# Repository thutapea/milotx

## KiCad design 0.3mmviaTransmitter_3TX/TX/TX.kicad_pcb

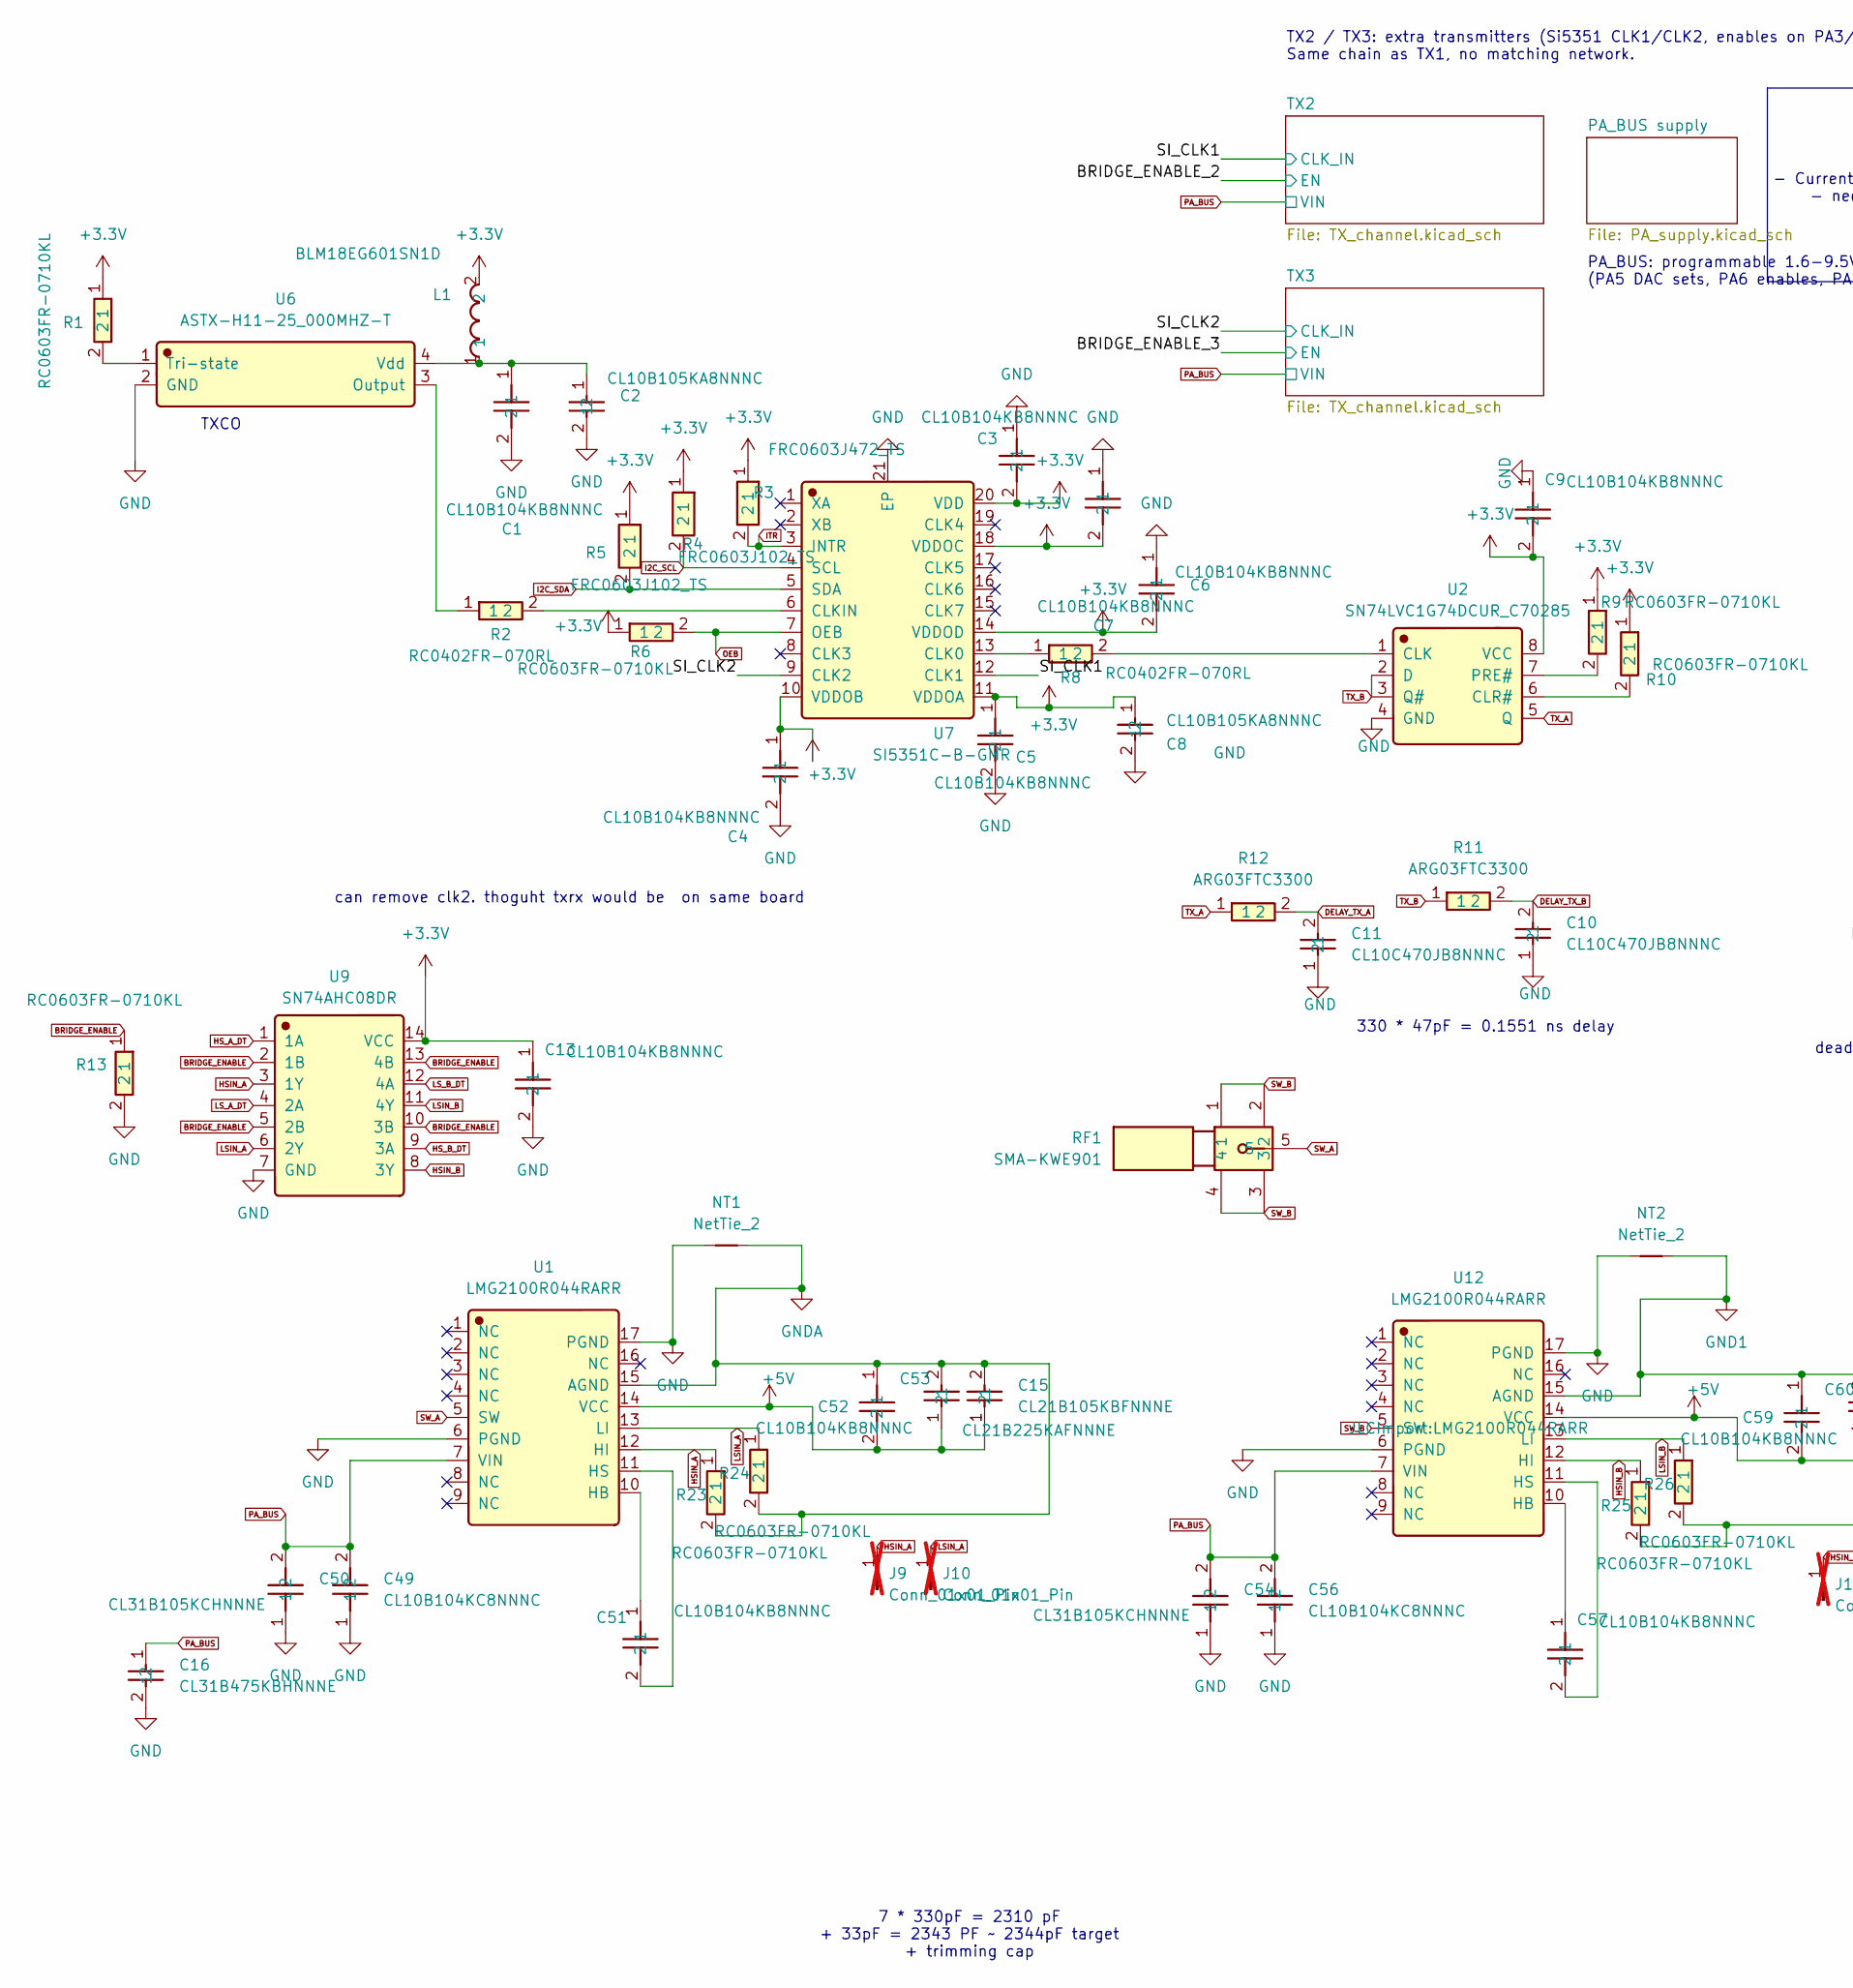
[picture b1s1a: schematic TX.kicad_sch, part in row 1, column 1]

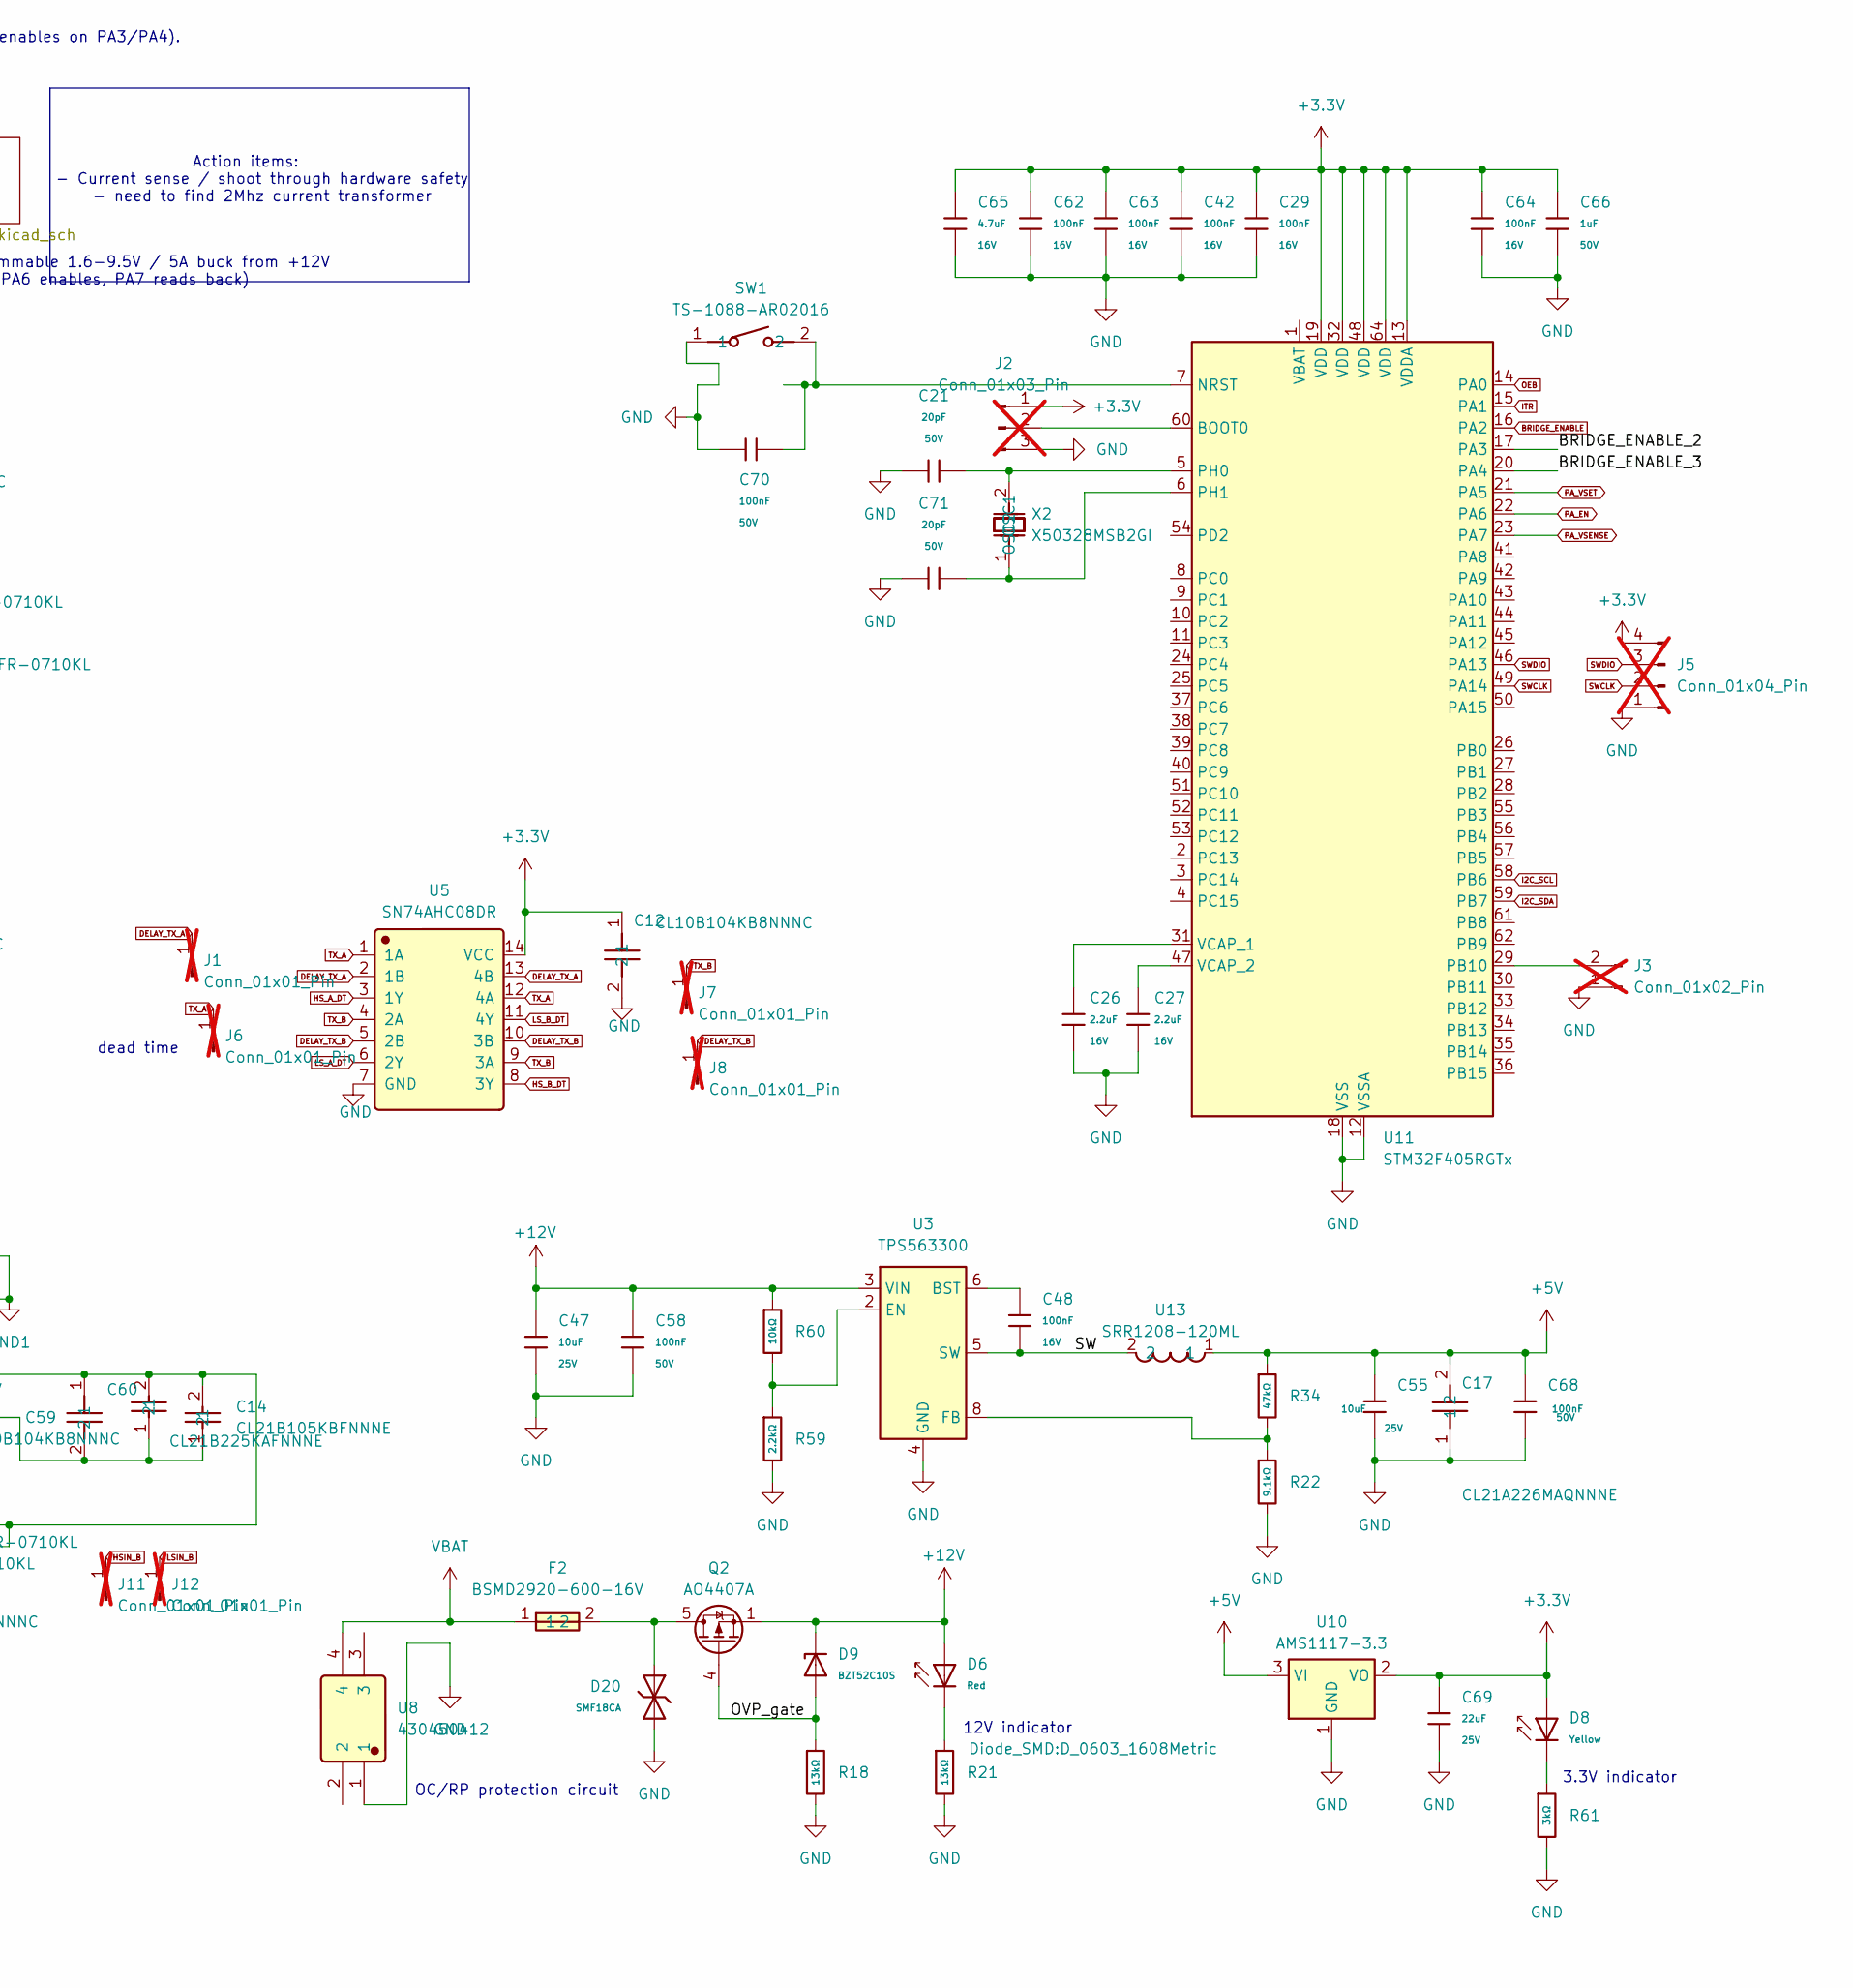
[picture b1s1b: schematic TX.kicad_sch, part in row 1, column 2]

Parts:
C1, C3, C4, C5, C6, C7, C9, C12, C13, C51, C52, C57, C59: CL10B104KB8NNNC; C_0603_1608Metric; Manufacturer Part CL10B104KB8NNNC; LCSC C1591
C2, C8: CL10B105KA8NNNC; C_0603_1608Metric; Manufacturer Part CL10B105KA8NNNC; LCSC C29936
C10, C11: CL10C470JB8NNNC; C_0603_1608Metric; Manufacturer Part CL10C470JB8NNNC; LCSC C1671
C14, C15: CL21B105KBFNNNE; C_0805_2012Metric; Manufacturer Part CL21B105KBFNNNE; LCSC C28323
C16: CL31B475KBHNNNE; C_1206_3216Metric; Manufacturer Part CL31B475KBHNNNE; LCSC C51205
C17: CL21A226MAQNNNE; C_0805_2012Metric; Manufacturer Part CL21A226MAQNNNE; LCSC C45783
C21, C71: 20pF; C_0402_1005Metric; Voltage Rated 50V; Tolerance ±5%; Part 0402CG200J500NT; LCSC C1554
C26, C27: 2.2uF; C_0603_1608Metric; Voltage Rated 16V; Tolerance ±10%; Part CL10A225KO8NNNC; LCSC C23630
C29, C42, C48, C62, C63, C64: 100nF; C_0402_1005Metric; Voltage Rated 16V; Tolerance ±10%; Part CL05B104KO5NNNC; LCSC C1525
C47, C55: 10uF; C_0603_1608Metric; Voltage Rated 25V; Tolerance ±20%; Part CL10A106MA8NRNC; LCSC C96446
C49, C56: CL10B104KC8NNNC; C_0603_1608Metric; Manufacturer Part CL10B104KC8NNNC; LCSC C15725
C50, C54: CL31B105KCHNNNE; C_1206_3216Metric; Manufacturer Part CL31B105KCHNNNE; LCSC C13832
C53, C60: CL21B225KAFNNNE; C_0805_2012Metric; Manufacturer Part CL21B225KAFNNNE; LCSC C19110
C58, C68, C70: 100nF; C_0603_1608Metric; Voltage Rated 50V; Tolerance ±10%; Part CC0603KRX7R9BB104; LCSC C14663
C65: 4.7uF; C_0603_1608Metric; Voltage Rated 16V; Tolerance ±10%; Part CL10A475KO8NNNC; LCSC C19666
C66: 1uF; C_0603_1608Metric; Voltage Rated 50V; Tolerance ±10%; Part CL10A105KB8NNNC; LCSC C15849
C69: 22uF; C_0805_2012Metric; Voltage Rated 25V; Tolerance ±20%; Part CL21A226MAQNNNE; LCSC C45783
D6: Red; D_0603_1608Metric; Part KT-0603R; LCSC C2286
D8: Yellow; D_0603_1608Metric; Forward Voltage (VF) 1.6V~2.6V; Part NCD0603Y2; LCSC C89811
D9: BZT52C10S; D_SOD-323; Part BZT52C10S; LCSC C19077446
D20: SMF18CA; D_SOD-123F; Breakdown Voltage 20V; Part SMF18CA; LCSC C19077513
F2: BSMD2920-600-16V; Manufacturer Part BSMD2920-600-16V; LCSC C910847
J1, J6, J7, J8, J9, J10, J11, J12: Conn_01x01_Pin; PinHeader_1x01_P2.54mm_Vertical; not fitted
J2: Conn_01x03_Pin; PinSocket_1x03_P2.54mm_Vertical; not fitted
J3: Conn_01x02_Pin; PinHeader_1x02_P2.54mm_Vertical; not fitted
J5: Conn_01x04_Pin; PinHeader_1x04_P2.54mm_Vertical; not fitted
L1: BLM18EG601SN1D; L_0603_1608Metric; Manufacturer Part BLM18EG601SN1D; LCSC C20345
NT1, NT2: NetTie_2; NetTie-2_SMD_Pad2.0mm
Q2: AO4407A; SOIC-8_3.9x4.9mm_P1.27mm; Manufacturer Part AO4407A; LCSC C2841482
R1, R6, R9, R10, R13, R23, R24, R25, R26: RC0603FR-0710KL; R_0603_1608Metric; Manufacturer Part RC0603FR-0710KL; LCSC C98220
R2, R8: RC0402FR-070RL; R_0402_1005Metric; Manufacturer Part RC0402FR-070RL; LCSC C106231
R3: FRC0603J472_TS; R_0603_1608Metric; Manufacturer Part FRC0603J472 TS; LCSC C2907166
R4, R5: FRC0603J102_TS; R_0603_1608Metric; Manufacturer Part FRC0603J102 TS; LCSC C2907113
R11, R12: ARG03FTC3300; R_0603_1608Metric; Manufacturer Part ARG03FTC3300; LCSC C217969
R18, R21: 13kΩ; R_0603_1608Metric; Overload Voltage (Max) 75V; Tolerance ±1%; Part 0603WAF1302T5E; LCSC C22797
R22: 9.1kΩ; R_0603_1608Metric; Overload Voltage (Max) 75V; Tolerance ±1%; Part 0603WAF9101T5E; LCSC C23260
R34: 47kΩ; R_0402_1005Metric; Overload Voltage (Max) 50V; Tolerance ±1%; Part 0402WGF4702TCE; LCSC C25792
R59: 2.2kΩ; R_0402_1005Metric; Overload Voltage (Max) 50V; Tolerance ±1%; Part 0402WGF2201TCE; LCSC C25879
R60: 10kΩ; R_0402_1005Metric; Overload Voltage (Max) 50V; Tolerance ±1%; Part 0402WGF1002TCE; LCSC C25744
R61: 3kΩ; R_0603_1608Metric; Overload Voltage (Max) 75V; Tolerance ±1%; Part 0603WAF3001T5E; LCSC C4211
RF1: SMA-KWE901; Manufacturer Part SMA-KWE901; LCSC C914553
SW1: TS-1088-AR02016; SW_PUSH_1P1T_6x3.5mm_H5.0_APEM_MJTP1250; Manufacturer Part TS-1088-AR02016; LCSC C54141293
U1, U12: LMG2100R044RARR; Manufacturer Part LMG2100R044RARR; LCSC C22453052
U2: SN74LVC1G74DCUR_C70285; VSSOP-8_2.3x2mm_P0.5mm; Manufacturer Part SN74LVC1G74DCUR; LCSC C70285
U3: TPS563300; SOT-583-8
U5, U9: SN74AHC08DR; SOIC-14_3.9x8.7mm_P1.27mm; Manufacturer Part SN74AHC08DR; LCSC C6937
U6: ASTX-H11-25_000MHZ-T; Crystal_SMD_3225-4Pin_3.2x2.5mm; Manufacturer Part ASTX-H11-25.000MHZ-T; LCSC C7217716
U7: SI5351C-B-GMR; Manufacturer Part SI5351C-B-GMR; LCSC C2649375
U8: 430450412; Molex_Micro-Fit_3.0_43045-0412_2x02_P3.00mm_Vertical; Manufacturer Part 430450412; LCSC C277721
U10: AMS1117-3.3; SOT-223-3_TabPin2
U11: STM32F405RGTx; LQFP-64_10x10mm_P0.5mm; LCSC C15742
U13: SRR1208-120ML; Manufacturer Part SRR1208-120ML; LCSC C1329356
X2: X50328MSB2GI; Crystal_SMD_5032-2Pin_5.0x3.2mm; Manufacturer Part X50328MSB2GI; LCSC C115962

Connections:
+3.3V: C3.2, C4.1, C5.1, C6.2, C7.2, C8.1, C9.2, C12.1, C13.1, C29.1, C42.1, C62.1, C63.1, C64.1, C65.1, C66.1, C69.1, D8.2, J2.1, J5.4, L1.2, R1.1, R3.1, R4.1, R5.1, R6.1, R9.1, R10.1, U2.8 (VCC), U5.14 (VCC), U7.10 (VDDOB), U7.11 (VDDOA), U7.14 (VDDOD), U7.18 (VDDOC), U7.20 (VDD), U9.14 (VCC), U10.2 (VO), U11.13 (VDDA), U11.19 (VDD), U11.32 (VDD), U11.48 (VDD), U11.64 (VDD); also elsewhere on the board
+5V: C14.1, C15.1, C17.2, C52.2, C53.1, C55.1, C59.2, C60.1, C68.1, R34.1, U1.14 (VCC), U10.3 (VI), U12.14 (VCC), U13.1; also elsewhere on the board
+12V: C47.1, C58.1, D6.2, D9.1, Q2.1 (S), Q2.2 (S), Q2.3 (S), R60.1, U3.3 (VIN); also elsewhere on the board
/BRIDGE_ENABLE_2: U11.17 (PA3); also elsewhere on the board
/BRIDGE_ENABLE_3: U11.20 (PA4); also elsewhere on the board
/OVP_gate: D9.2, Q2.4 (G), R18.1
/SI_CLK1: U7.12 (CLK1); also elsewhere on the board
/SI_CLK2: U7.9 (CLK2); also elsewhere on the board
/SW: C48.2, U3.5 (SW), U13.2
BRIDGE_ENABLE: R13.1, U9.2 (1B), U9.5 (2B), U9.10 (3B), U9.13 (4B), U11.16 (PA2)
DELAY_TX_A: C11.2, J1.1 (Pin_1_1), R12.2, U5.2 (1B), U5.13 (4B)
DELAY_TX_B: C10.2, J8.1 (Pin_1_1), R11.2, U5.5 (2B), U5.10 (3B)
GND: C1.2, C2.2, C3.1, C4.2, C5.2, C6.1, C7.1, C8.2, C9.1, C10.1, C11.1, C12.2, C13.2, C16.2, C17.1, C21.1, C26.2, C27.2, C29.2, C42.2, C47.2, C49.1, C50.1, C54.1, C55.2, C56.1, C58.2, C62.2, C63.2, C64.2, C65.2, C66.2, C68.2, C69.2, C70.2, C71.1, D20.1, J2.3, J3.1, J5.1, NT1.1, NT2.1, R13.2, R18.2, R21.2, R22.2, R59.2, R61.2, SW1.1, U1.6 (PGND), U1.17 (PGND), U2.4 (GND), U3.4 (GND), U5.7 (GND), U6.2 (GND), U7.21 (EP), U8.1, U9.7 (GND), U10.1 (GND), U11.12 (VSSA), U11.18 (VSS), U11.63 (VSS), U12.6 (PGND), U12.17 (PGND); also elsewhere on the board
GND1: C14.2, C59.1, C60.2, NT2.2, R25.2, R26.2, U12.15 (AGND)
GNDA: C15.2, C52.1, C53.2, NT1.2, R23.2, R24.2, U1.15 (AGND)
HSIN_A: J9.1 (Pin_1_1), R23.1, U1.12 (HI), U9.3 (1Y)
HSIN_B: J11.1 (Pin_1_1), R25.1, U9.8 (3Y), U12.12 (HI)
HS_A_DT: U5.3 (1Y), U9.1 (1A)
HS_B_DT: U5.8 (3Y), U9.9 (3A)
I2C_SCL: R4.2, U7.4 (SCL), U11.58 (PB6)
I2C_SDA: R5.2, U7.5 (SDA), U11.59 (PB7)
ITR: R3.2, U7.3 (INTR), U11.15 (PA1)
LSIN_A: J10.1 (Pin_1_1), R24.1, U1.13 (LI), U9.6 (2Y)
LSIN_B: J12.1 (Pin_1_1), R26.1, U9.11 (4Y), U12.13 (LI)
LS_A_DT: U5.6 (2Y), U9.4 (2A)
LS_B_DT: U5.11 (4Y), U9.12 (4A)
unnamed: D6.1, R21.1
unnamed: D8.1, R61.1
unnamed: D20.2, F2.2, Q2.5 (D), Q2.6 (D), Q2.7 (D), Q2.8 (D)
unnamed: J2.2, U11.60 (BOOT0)
unnamed: J3.2, U11.29 (PB10)
unnamed: C51.1, U1.10 (HB)
unnamed: C51.2, U1.11 (HS)
unnamed: R8.2, U2.1 (CLK)
unnamed: R9.2, U2.6 (CLR#)
unnamed: R10.2, U2.7 (PRE#)
unnamed: C48.1, U3.6 (BST)
unnamed: R59.1, R60.2, U3.2 (EN)
unnamed 90: R22.1, R34.2, U3.8 (FB); also elsewhere on the board
unnamed: R2.1, U6.3 (Output)
unnamed: R1.2, U6.1 (Tri-state)
unnamed: C1.1, C2.1, L1.1, U6.4 (Vdd)
unnamed: R8.1, U7.13 (CLK0)
unnamed: R2.2, U7.6 (CLKIN)
unnamed: C70.1, SW1.2, U11.7 (NRST)
unnamed: C21.2, U11.5 (PH0), X2.2 (OSC2)
unnamed: C71.2, U11.6 (PH1), X2.1 (OSC1)
unnamed: C26.1, U11.31 (VCAP_1)
unnamed: C27.1, U11.47 (VCAP_2)
unnamed: C57.1, U12.10 (HB)
unnamed: C57.2, U12.11 (HS)
OEB: R6.2, U7.7 (OEB), U11.14 (PA0)
PA_BUS: C16.1, C49.2, C50.2, C54.2, C56.2, U1.7 (VIN), U12.7 (VIN); also elsewhere on the board
PA_EN: U11.22 (PA6); also elsewhere on the board
PA_VSENSE: U11.23 (PA7); also elsewhere on the board
PA_VSET: U11.21 (PA5); also elsewhere on the board
SWCLK: J5.2, U11.49 (PA14)
SWDIO: J5.3, U11.46 (PA13)
SW_A: RF1.5, U1.5 (SW)
SW_B: RF1.1, RF1.2, RF1.3, RF1.4, U12.5 (SW)
TX_A: J6.1 (Pin_1_1), R12.1, U2.5 (Q), U5.1 (1A), U5.12 (4A)
TX_B: J7.1 (Pin_1_1), R11.1, U2.2 (D), U2.3 (Q#), U5.4 (2A), U5.9 (3A)
VBAT: F2.1, U8.4

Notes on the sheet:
TXCO
Action items: - Current sense / shoot through hardware safety - need to find 2Mhz current transformer
7 * 330pF = 2310 pF + 33pF = 2343 PF ~ 2344pF target + trimming cap
330 * 47pF = 0.1551 ns delay
12V indicator
OC/RP protection circuit
dead time
can remove clk2. thoguht txrx would be on same board
3.3V indicator
TX2 / TX3: extra transmitters (Si5351 CLK1/CLK2, enables on PA3/PA4). Same chain as TX1, no matching network.
PA_BUS: programmable 1.6-9.5V / 5A buck from +12V (PA5 DAC sets, PA6 enables, PA7 reads back)

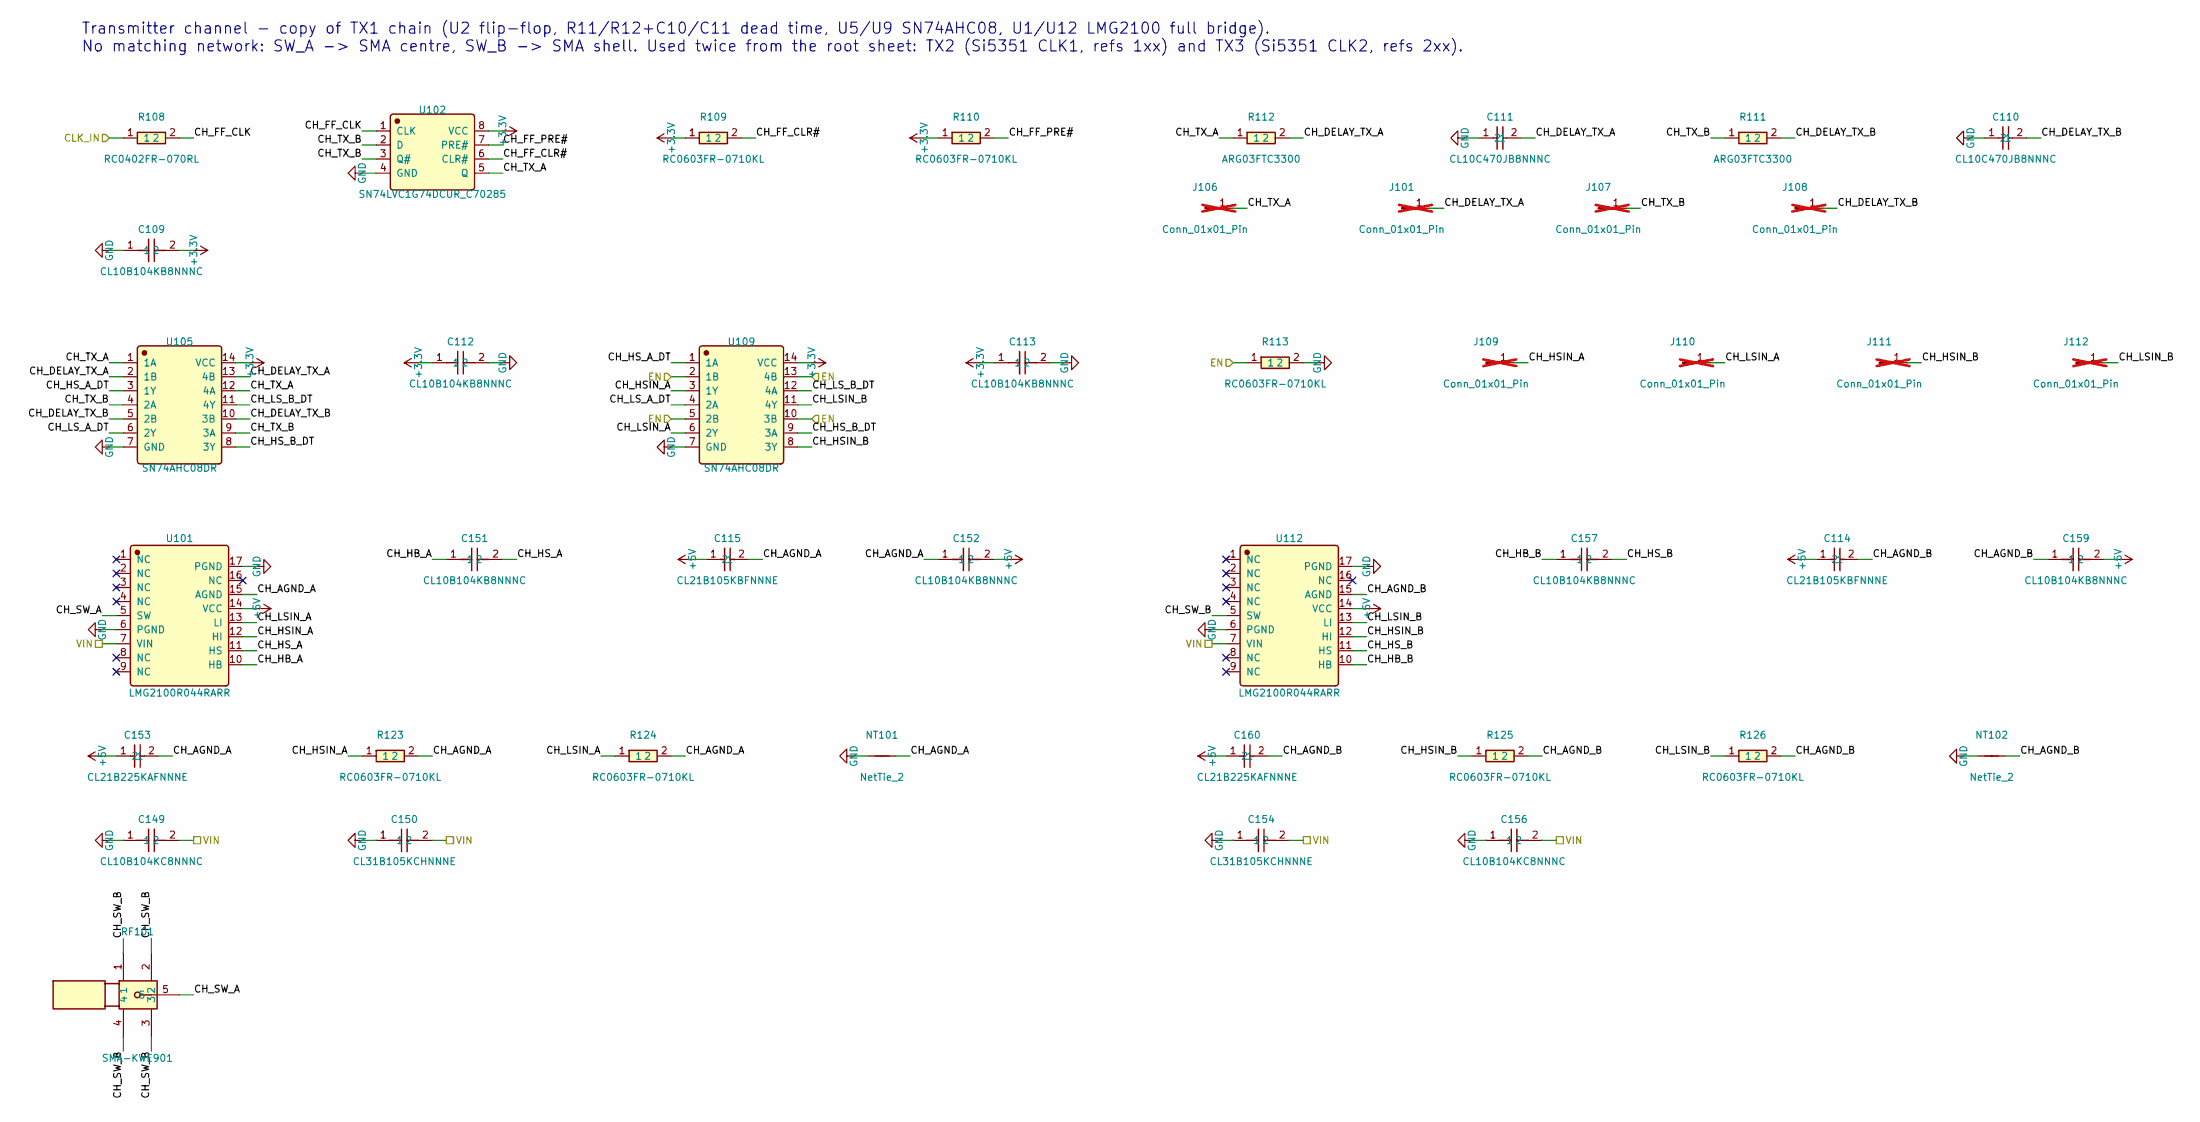
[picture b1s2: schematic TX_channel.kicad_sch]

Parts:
C109, C112, C113, C151, C152, C157, C159: CL10B104KB8NNNC; C_0603_1608Metric; Manufacturer Part CL10B104KB8NNNC; LCSC C1591
C110, C111: CL10C470JB8NNNC; C_0603_1608Metric; Manufacturer Part CL10C470JB8NNNC; LCSC C1671
C114, C115: CL21B105KBFNNNE; C_0805_2012Metric; Manufacturer Part CL21B105KBFNNNE; LCSC C28323
C149, C156: CL10B104KC8NNNC; C_0603_1608Metric; Manufacturer Part CL10B104KC8NNNC; LCSC C15725
C150, C154: CL31B105KCHNNNE; C_1206_3216Metric; Manufacturer Part CL31B105KCHNNNE; LCSC C13832
C153, C160: CL21B225KAFNNNE; C_0805_2012Metric; Manufacturer Part CL21B225KAFNNNE; LCSC C19110
J101, J106, J107, J108, J109, J110, J111, J112: Conn_01x01_Pin; PinHeader_1x01_P2.54mm_Vertical; not fitted
NT101, NT102: NetTie_2; NetTie-2_SMD_Pad2.0mm
R108: RC0402FR-070RL; R_0402_1005Metric; Manufacturer Part RC0402FR-070RL; LCSC C106231
R109, R110, R113, R123, R124, R125, R126: RC0603FR-0710KL; R_0603_1608Metric; Manufacturer Part RC0603FR-0710KL; LCSC C98220
R111, R112: ARG03FTC3300; R_0603_1608Metric; Manufacturer Part ARG03FTC3300; LCSC C217969
RF101: SMA-KWE901; Manufacturer Part SMA-KWE901; LCSC C914553
U101, U112: LMG2100R044RARR; Manufacturer Part LMG2100R044RARR; LCSC C22453052
U102: SN74LVC1G74DCUR_C70285; VSSOP-8_2.3x2mm_P0.5mm; Manufacturer Part SN74LVC1G74DCUR; LCSC C70285
U105, U109: SN74AHC08DR; SOIC-14_3.9x8.7mm_P1.27mm; Manufacturer Part SN74AHC08DR; LCSC C6937

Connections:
+3.3V: C109.2, C112.1, C113.1, R109.1, R110.1, U102.8 (VCC), U105.14 (VCC), U109.14 (VCC); also elsewhere on the board
+5V: C114.1, C115.1, C152.2, C153.1, C159.2, C160.1, U101.14 (VCC), U112.14 (VCC); also elsewhere on the board
/BRIDGE_ENABLE_2: R113.1, U109.2 (1B), U109.5 (2B), U109.10 (3B), U109.13 (4B); also elsewhere on the board
/SI_CLK1: R108.1; also elsewhere on the board
/TX2/CH_AGND_A: C115.2, C152.1, C153.2, NT101.2, R123.2, R124.2, U101.15 (AGND)
/TX2/CH_AGND_B: C114.2, C159.1, C160.2, NT102.2, R125.2, R126.2, U112.15 (AGND)
/TX2/CH_DELAY_TX_A: C111.2, J101.1 (Pin_1_1), R112.2, U105.2 (1B), U105.13 (4B)
/TX2/CH_DELAY_TX_B: C110.2, J108.1 (Pin_1_1), R111.2, U105.5 (2B), U105.10 (3B)
/TX2/CH_FF_CLK: R108.2, U102.1 (CLK)
/TX2/CH_FF_CLR#: R109.2, U102.6 (CLR#)
/TX2/CH_FF_PRE#: R110.2, U102.7 (PRE#)
/TX2/CH_HB_A: C151.1, U101.10 (HB)
/TX2/CH_HB_B: C157.1, U112.10 (HB)
/TX2/CH_HSIN_A: J109.1 (Pin_1_1), R123.1, U101.12 (HI), U109.3 (1Y)
/TX2/CH_HSIN_B: J111.1 (Pin_1_1), R125.1, U109.8 (3Y), U112.12 (HI)
/TX2/CH_HS_A: C151.2, U101.11 (HS)
/TX2/CH_HS_A_DT: U105.3 (1Y), U109.1 (1A)
/TX2/CH_HS_B: C157.2, U112.11 (HS)
/TX2/CH_HS_B_DT: U105.8 (3Y), U109.9 (3A)
/TX2/CH_LSIN_A: J110.1 (Pin_1_1), R124.1, U101.13 (LI), U109.6 (2Y)
/TX2/CH_LSIN_B: J112.1 (Pin_1_1), R126.1, U109.11 (4Y), U112.13 (LI)
/TX2/CH_LS_A_DT: U105.6 (2Y), U109.4 (2A)
/TX2/CH_LS_B_DT: U105.11 (4Y), U109.12 (4A)
/TX2/CH_SW_A: RF101.5, U101.5 (SW)
/TX2/CH_SW_B: RF101.1, RF101.2, RF101.3, RF101.4, U112.5 (SW)
/TX2/CH_TX_A: J106.1 (Pin_1_1), R112.1, U102.5 (Q), U105.1 (1A), U105.12 (4A)
/TX2/CH_TX_B: J107.1 (Pin_1_1), R111.1, U102.2 (D), U102.3 (Q#), U105.4 (2A), U105.9 (3A)
GND: C109.1, C110.1, C111.1, C112.2, C113.2, C149.1, C150.1, C154.1, C156.1, NT101.1, NT102.1, R113.2, U101.6 (PGND), U101.17 (PGND), U102.4 (GND), U105.7 (GND), U109.7 (GND), U112.6 (PGND), U112.17 (PGND); also elsewhere on the board
PA_BUS: C149.2, C150.2, C154.2, C156.2, U101.7 (VIN), U112.7 (VIN); also elsewhere on the board

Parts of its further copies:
C209, C212, C213, C251, C252, C257, C259: CL10B104KB8NNNC; C_0603_1608Metric; Manufacturer Part CL10B104KB8NNNC; LCSC C1591
C210, C211: CL10C470JB8NNNC; C_0603_1608Metric; Manufacturer Part CL10C470JB8NNNC; LCSC C1671
C214, C215: CL21B105KBFNNNE; C_0805_2012Metric; Manufacturer Part CL21B105KBFNNNE; LCSC C28323
C249, C256: CL10B104KC8NNNC; C_0603_1608Metric; Manufacturer Part CL10B104KC8NNNC; LCSC C15725
C250, C254: CL31B105KCHNNNE; C_1206_3216Metric; Manufacturer Part CL31B105KCHNNNE; LCSC C13832
C253, C260: CL21B225KAFNNNE; C_0805_2012Metric; Manufacturer Part CL21B225KAFNNNE; LCSC C19110
J201, J206, J207, J208, J209, J210, J211, J212: Conn_01x01_Pin; PinHeader_1x01_P2.54mm_Vertical; not fitted
NT201, NT202: NetTie_2; NetTie-2_SMD_Pad2.0mm
R208: RC0402FR-070RL; R_0402_1005Metric; Manufacturer Part RC0402FR-070RL; LCSC C106231
R209, R210, R213, R223, R224, R225, R226: RC0603FR-0710KL; R_0603_1608Metric; Manufacturer Part RC0603FR-0710KL; LCSC C98220
R211, R212: ARG03FTC3300; R_0603_1608Metric; Manufacturer Part ARG03FTC3300; LCSC C217969
RF201: SMA-KWE901; Manufacturer Part SMA-KWE901; LCSC C914553
U201, U212: LMG2100R044RARR; Manufacturer Part LMG2100R044RARR; LCSC C22453052
U202: SN74LVC1G74DCUR_C70285; VSSOP-8_2.3x2mm_P0.5mm; Manufacturer Part SN74LVC1G74DCUR; LCSC C70285
U205, U209: SN74AHC08DR; SOIC-14_3.9x8.7mm_P1.27mm; Manufacturer Part SN74AHC08DR; LCSC C6937

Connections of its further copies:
+3.3V: C209.2, C212.1, C213.1, R209.1, R210.1, U202.8 (VCC), U205.14 (VCC), U209.14 (VCC); also elsewhere on the board
+5V: C214.1, C215.1, C252.2, C253.1, C259.2, C260.1, U201.14 (VCC), U212.14 (VCC); also elsewhere on the board
/BRIDGE_ENABLE_3: R213.1, U209.2 (1B), U209.5 (2B), U209.10 (3B), U209.13 (4B); also elsewhere on the board
/SI_CLK2: R208.1; also elsewhere on the board
/TX3/CH_AGND_A: C215.2, C252.1, C253.2, NT201.2, R223.2, R224.2, U201.15 (AGND)
/TX3/CH_AGND_B: C214.2, C259.1, C260.2, NT202.2, R225.2, R226.2, U212.15 (AGND)
/TX3/CH_DELAY_TX_A: C211.2, J201.1 (Pin_1_1), R212.2, U205.2 (1B), U205.13 (4B)
/TX3/CH_DELAY_TX_B: C210.2, J208.1 (Pin_1_1), R211.2, U205.5 (2B), U205.10 (3B)
/TX3/CH_FF_CLK: R208.2, U202.1 (CLK)
/TX3/CH_FF_CLR#: R209.2, U202.6 (CLR#)
/TX3/CH_FF_PRE#: R210.2, U202.7 (PRE#)
/TX3/CH_HB_A: C251.1, U201.10 (HB)
/TX3/CH_HB_B: C257.1, U212.10 (HB)
/TX3/CH_HSIN_A: J209.1 (Pin_1_1), R223.1, U201.12 (HI), U209.3 (1Y)
/TX3/CH_HSIN_B: J211.1 (Pin_1_1), R225.1, U209.8 (3Y), U212.12 (HI)
/TX3/CH_HS_A: C251.2, U201.11 (HS)
/TX3/CH_HS_A_DT: U205.3 (1Y), U209.1 (1A)
/TX3/CH_HS_B: C257.2, U212.11 (HS)
/TX3/CH_HS_B_DT: U205.8 (3Y), U209.9 (3A)
/TX3/CH_LSIN_A: J210.1 (Pin_1_1), R224.1, U201.13 (LI), U209.6 (2Y)
/TX3/CH_LSIN_B: J212.1 (Pin_1_1), R226.1, U209.11 (4Y), U212.13 (LI)
/TX3/CH_LS_A_DT: U205.6 (2Y), U209.4 (2A)
/TX3/CH_LS_B_DT: U205.11 (4Y), U209.12 (4A)
/TX3/CH_SW_A: RF201.5, U201.5 (SW)
/TX3/CH_SW_B: RF201.1, RF201.2, RF201.3, RF201.4, U212.5 (SW)
/TX3/CH_TX_A: J206.1 (Pin_1_1), R212.1, U202.5 (Q), U205.1 (1A), U205.12 (4A)
/TX3/CH_TX_B: J207.1 (Pin_1_1), R211.1, U202.2 (D), U202.3 (Q#), U205.4 (2A), U205.9 (3A)
GND: C209.1, C210.1, C211.1, C212.2, C213.2, C249.1, C250.1, C254.1, C256.1, NT201.1, NT202.1, R213.2, U201.6 (PGND), U201.17 (PGND), U202.4 (GND), U205.7 (GND), U209.7 (GND), U212.6 (PGND), U212.17 (PGND); also elsewhere on the board
PA_BUS: C249.2, C250.2, C254.2, C256.2, U201.7 (VIN), U212.7 (VIN); also elsewhere on the board

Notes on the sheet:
Transmitter channel - copy of TX1 chain (U2 flip-flop, R11/R12+C10/C11 dead time, U5/U9 SN74AHC08, U1/U12 LMG2100 full bridge). No matching network: SW_A -> SMA centre, SW_B -> SMA shell. Used twice from the root sheet: TX2 (Si5351 CLK1, refs 1xx) and TX3 (Si5351 CLK2, refs 2xx).
